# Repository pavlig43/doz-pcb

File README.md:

# doz — плата дозатора

Проект платы в KiCad 10.

- `doz.kicad_pro`, `doz.kicad_sch`, `doz.kicad_pcb` — исходники проекта.
- `doz-B_Cu.pdf` — чертёж нижнего слоя для печати.
- `bom/ibom.html` — интерактивная ведомость деталей.
- `doz.ses`, `doz.rules` — результат и правила Freerouting.

Для правки знаков и посадочных мест нужны библиотеки `TrueLib` и `PCM_SparkFun`, подключённые в KiCad. Плата и схема хранят свои копии используемых элементов и открываются без этих библиотек.

Перед изготовлением проверьте правила платы в KiCad и печатайте PDF с масштабом 100 %.

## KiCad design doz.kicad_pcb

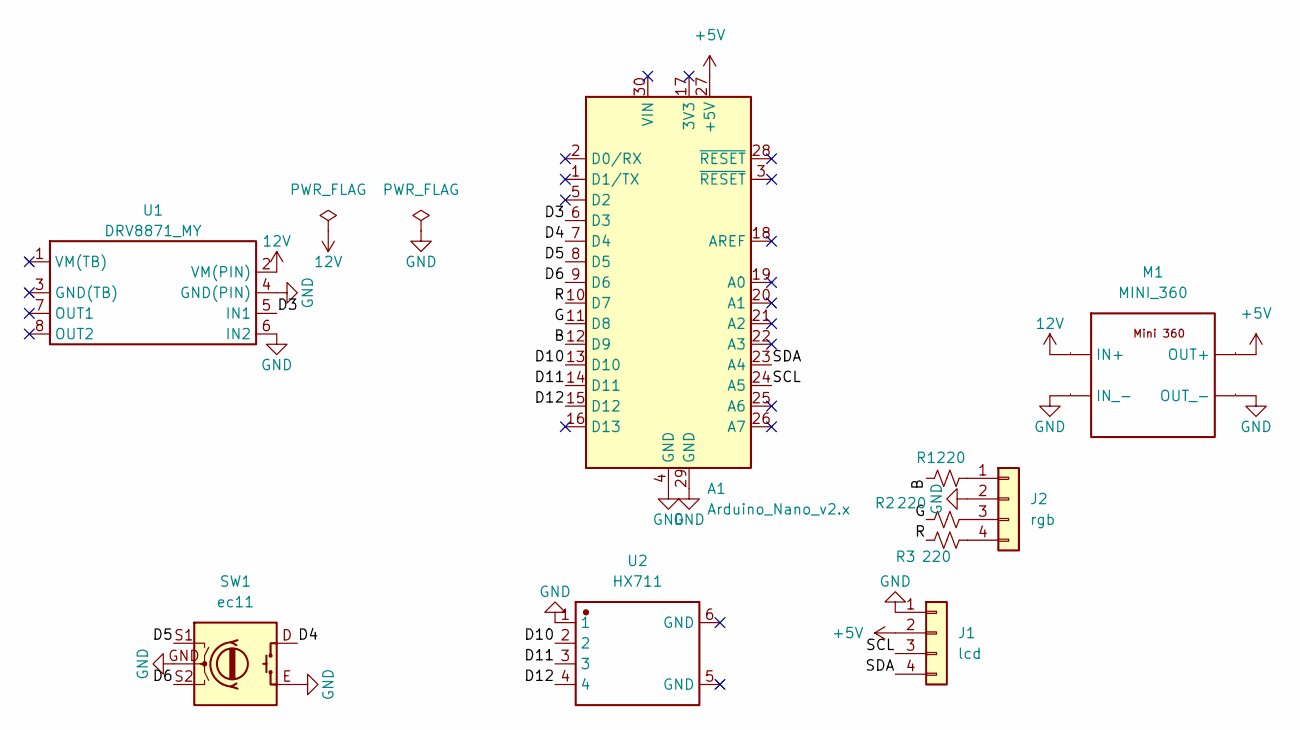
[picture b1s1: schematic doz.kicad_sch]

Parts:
A1: Arduino_Nano_v2.x; Arduino_Nano
J1: lcd; PinHeader_1x04_P2.54mm_Horizontal
J2: rgb; PinHeader_1x04_P2.54mm_Vertical
M1: MINI_360; MINI_360MY_TRUE
R1, R2, R3: 220; R_1206_3216Metric
SW1: ec11; EC11_MY
U1: DRV8871_MY; Manufacturer Part DRV8871
U2: HX711; USB_A_TH_MOLEX_67643_3910; Manufacturer Part 67643-3910

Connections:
12V: M1.3 (IN+), U1.2 (VM(PIN))
+5V: A1.27 (+5V), J1.2, M1.1 (OUT+)
/B: A1.12 (D9), R1.1
/D3: A1.6 (D3), U1.5 (IN1)
/D4: A1.7 (D4), SW1.D
/D5: A1.8 (D5), SW1.S1
/D6: A1.9 (D6), SW1.S2
/D10: A1.13 (D10), U2.2
/D11: A1.14 (D11), U2.3
/D12: A1.15 (D12), U2.4
/G: A1.11 (D8), R2.1
/R: A1.10 (D7), R3.1
/SCL: A1.24 (A5), J1.3
/SDA: A1.23 (A4), J1.4
GND: A1.4 (GND), A1.29 (GND), J1.1, J2.2, M1.2 (OUT_-), M1.4 (IN_-), SW1.E, SW1.GND, U1.4 (GND(PIN)), U1.6 (IN2), U2.1
unnamed: J2.1, R1.2
unnamed: J2.3, R2.2
unnamed: J2.4, R3.2

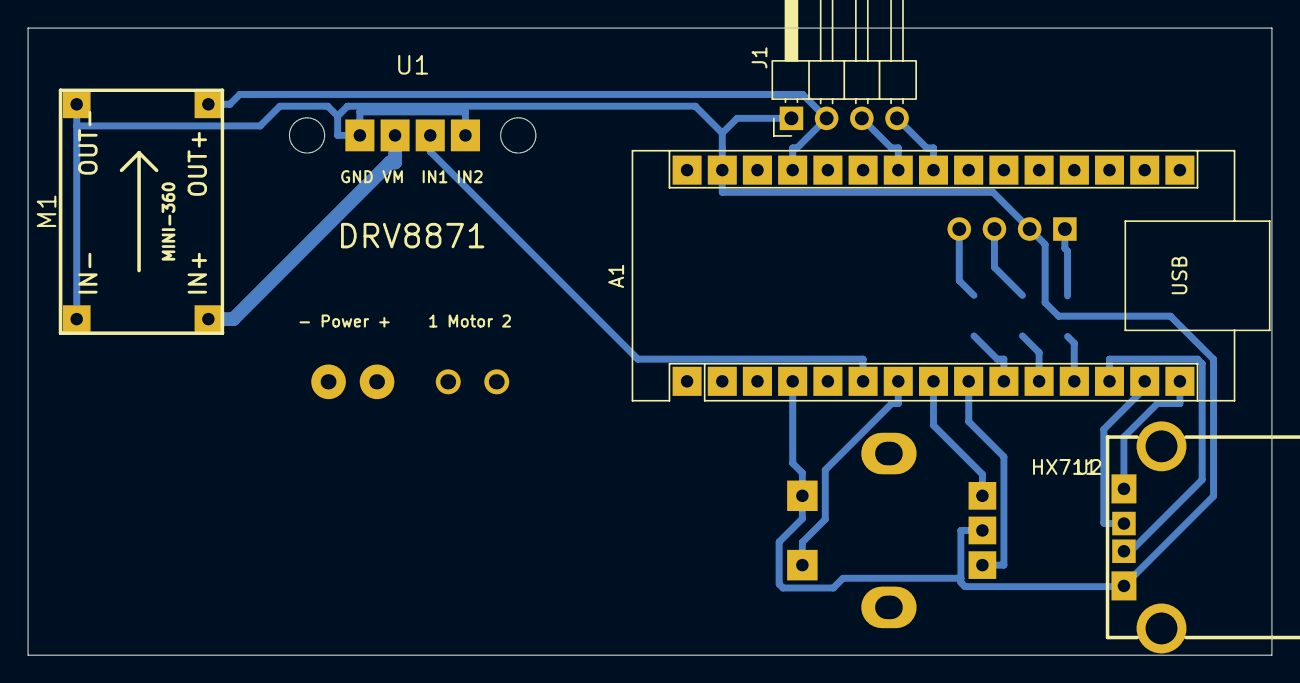
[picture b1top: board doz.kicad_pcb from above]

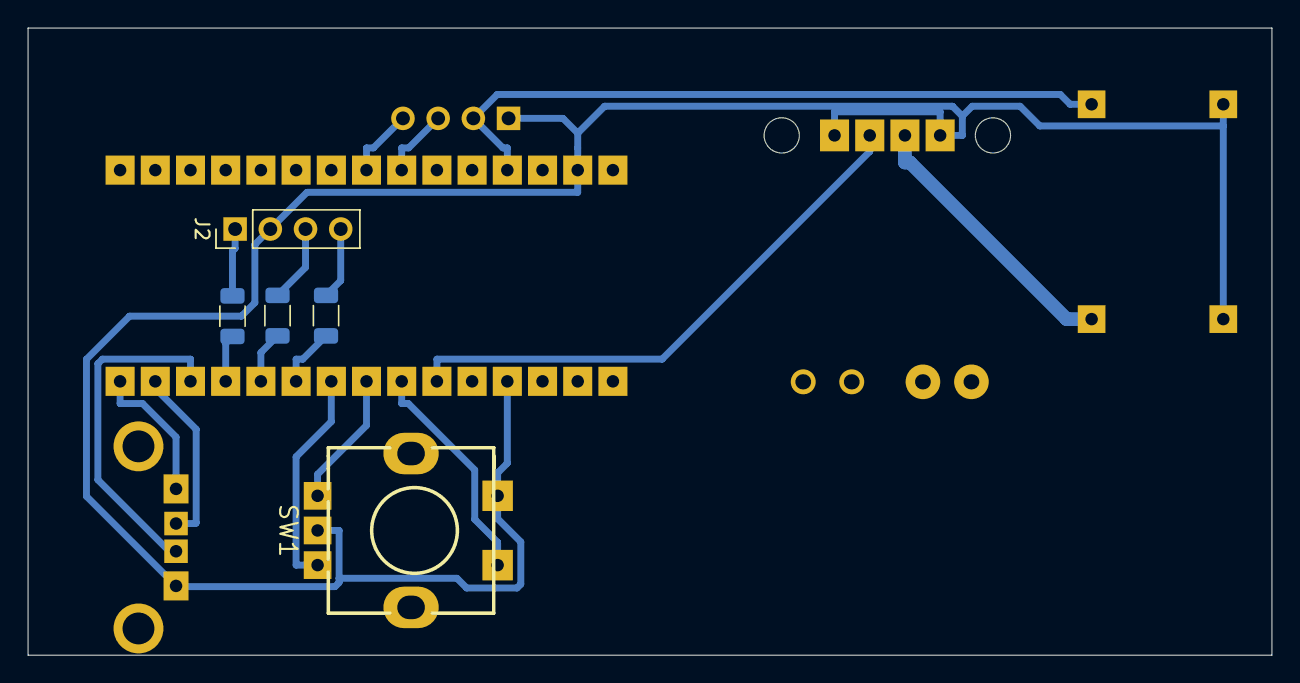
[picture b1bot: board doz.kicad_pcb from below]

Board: 2 copper layers, 89.8 x 45.2 mm, 10 parts (5 on the bottom side), 18 nets.
